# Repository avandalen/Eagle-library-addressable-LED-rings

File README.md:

# Eagle library for easily create addressable LED rings NeoPixel WS2812B-2020
See the article:
https://www.avdweb.nl/tech-tips/pcb/led-rings

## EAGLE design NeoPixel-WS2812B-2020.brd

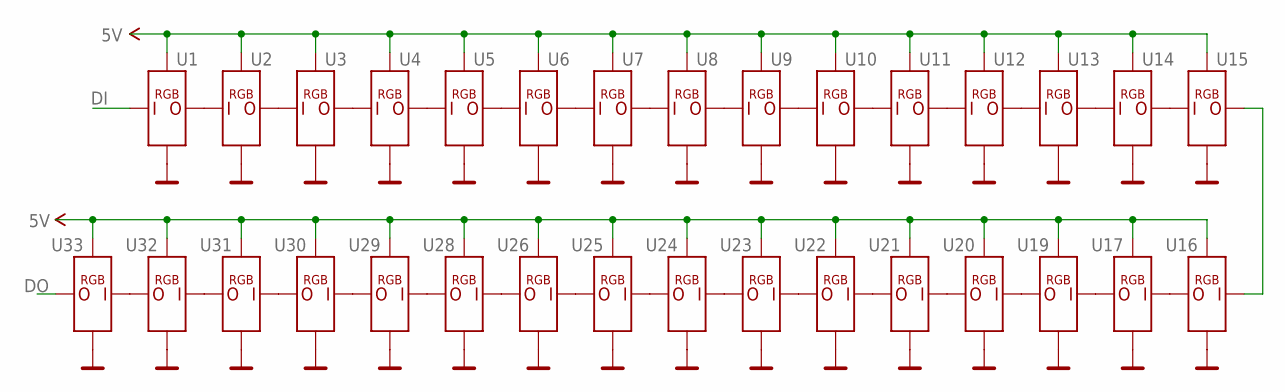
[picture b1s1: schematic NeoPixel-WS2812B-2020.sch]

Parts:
U1, U2, U3, U4, U5, U6, U7, U8, U9, U10, U11, U12, U13, U14, U15, U16, U17, U19, U20, U21, U22, U23, U24, U25, U26, U28, U29, U30, U31, U32, U33: LED-ADDRESSABLE16MM; LED-WS2812B-2020-RING

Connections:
5V: U1.+ (VDD), U2.+ (VDD), U3.+ (VDD), U4.+ (VDD), U5.+ (VDD), U6.+ (VDD), U7.+ (VDD), U8.+ (VDD), U9.+ (VDD), U10.+ (VDD), U11.+ (VDD), U12.+ (VDD), U13.+ (VDD), U14.+ (VDD), U15.+ (VDD), U16.+ (VDD), U17.+ (VDD), U19.+ (VDD), U20.+ (VDD), U21.+ (VDD), U22.+ (VDD), U23.+ (VDD), U24.+ (VDD), U25.+ (VDD), U26.+ (VDD), U28.+ (VDD), U29.+ (VDD), U30.+ (VDD), U31.+ (VDD), U32.+ (VDD), U33.+ (VDD)
DI: U1.DI
DO: U33.DO
GND: U1.GND, U2.GND, U3.GND, U4.GND, U5.GND, U6.GND, U7.GND, U8.GND, U9.GND, U10.GND, U11.GND, U12.GND, U13.GND, U14.GND, U15.GND, U16.GND, U17.GND, U19.GND, U20.GND, U21.GND, U22.GND, U23.GND, U24.GND, U25.GND, U26.GND, U28.GND, U29.GND, U30.GND, U31.GND, U32.GND, U33.GND
unnamed: U32.DO, U33.DI
unnamed: U31.DO, U32.DI
unnamed: U28.DO, U29.DI
unnamed: U29.DO, U30.DI
unnamed: U30.DO, U31.DI
unnamed: U19.DO, U20.DI
unnamed: U25.DO, U26.DI
unnamed: U24.DO, U25.DI
unnamed: U21.DO, U22.DI
unnamed: U22.DO, U23.DI
unnamed: U23.DO, U24.DI
unnamed: U17.DO, U19.DI
unnamed: U14.DO, U15.DI
unnamed: U13.DO, U14.DI
unnamed: U16.DO, U17.DI
unnamed: U10.DO, U11.DI
unnamed: U11.DO, U12.DI
unnamed: U12.DO, U13.DI
unnamed: U8.DO, U9.DI
unnamed: U7.DO, U8.DI
unnamed: U4.DO, U5.DI
unnamed: U5.DO, U6.DI
unnamed: U6.DO, U7.DI
unnamed: U2.DO, U3.DI
unnamed: U1.DO, U2.DI
unnamed: U9.DO, U10.DI
unnamed: U26.DO, U28.DI
unnamed: U20.DO, U21.DI
unnamed: U15.DO, U16.DI
unnamed: U3.DO, U4.DI

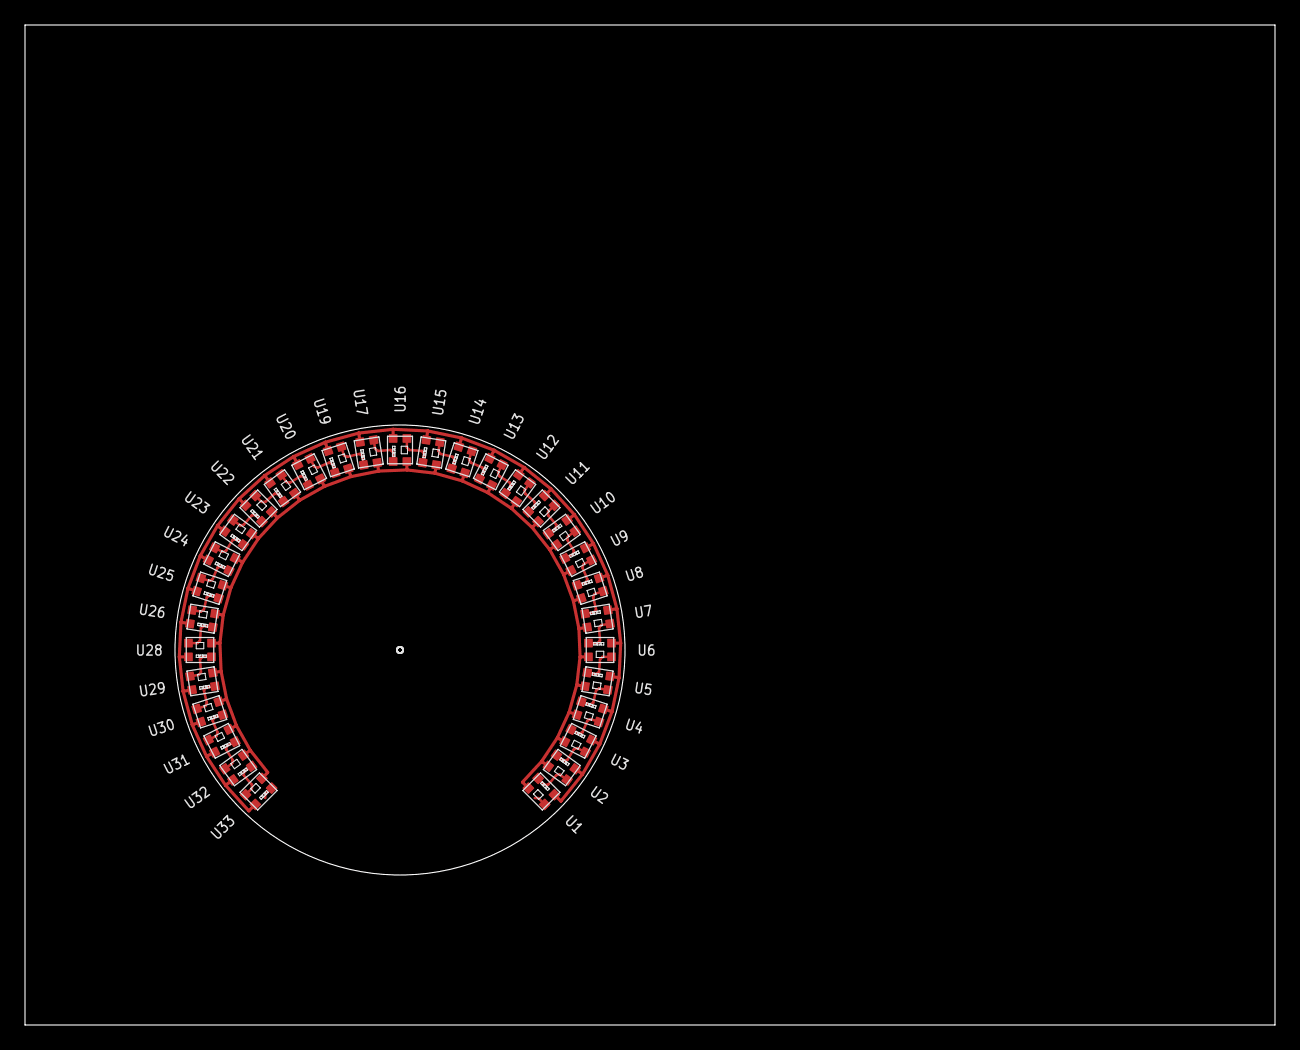
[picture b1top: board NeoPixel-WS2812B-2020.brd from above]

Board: 2 copper layers, 100.0 x 80.0 mm, 31 parts (0 on the bottom side), 32 nets.
